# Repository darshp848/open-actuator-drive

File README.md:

# Open actuator drive

KiCad designs and simulation models for a nominal 48 V brushless actuator
drive and its support electronics. See the [humanoid upper-body project
page](https://darshpatel.xyz/projects/humanoid-upper-body) for board renders,
system context, and the simulations behind the designs.

**All designs in this repository are unfinished, unvalidated research prototypes.**
No hardware validation has been performed. Routing and KiCad checks describe the
state of the design files. Fabrication, assembly, and hardware bring-up and
testing are still open.

## Boards

| Board | KiCad source and notes | Gerbers and drill | Current state |
|---|---|---|---|
| DC bus support | [180 × 45 mm board](hardware/support-board/) | [ZIP](fab/support-board/SupportBoard/SupportBoard-gerbers.zip) | Routed. No DRC findings or open connections. Three ERC library-symbol warnings. |
| Brake resistor Rev B | [190 × 38 mm strip](hardware/brake-resistor/) | [ZIP](fab/brake-resistor/BrakeResistor/BrakeResistor-gerbers.zip) | Routed. No DRC or ERC findings. Strip cooling and the thermostat interlock need testing. |
| External capacitor bank | [101.6 × 25.4 mm board](hardware/capacitor-bank/) | [ZIP](fab/capacitor-bank/CapacitorBank/CapacitorBank-gerbers.zip) | Routed. No DRC or ERC findings. Capacitor fit and electrical behavior need testing. |
| DF40 header breakout | [Bench breakout](hardware/df40-breakouts/DF40_Header_Breakout/) | [ZIP](fab/df40-breakouts/DF40_Header_Breakout/DF40_Header_Breakout-gerbers.zip) | Routed. No DRC or ERC findings. Mating orientation and fit need checking. |
| DF40 receptacle breakout | [Bench breakout](hardware/df40-breakouts/DF40_Receptacle_Breakout/) | [ZIP](fab/df40-breakouts/DF40_Receptacle_Breakout/DF40_Receptacle_Breakout-gerbers.zip) | Routed. No DRC or ERC findings. Mating orientation and fit need checking. |
| Common logic | [Controller stack draft](hardware/wip/logic-board/) | | Partially routed, 177 unconnected items. |
| P96 power (GIM8115-36 / GIM8108-36) | [Controller stack draft](hardware/wip/power-p96/) | | Partially routed, 212 unconnected items and one silkscreen DRC finding. |
| WGG power (WGG8108-8) | [Controller stack draft](hardware/wip/power-wgg/) | | Partially routed, 258 unconnected items. |

Open each project's `.kicad_pro` in KiCad 10. The five routed boards also have
schematic PDFs, BOMs and position files. See [fabrication files](fab/) for
export settings and the scope of the checks. See the [DF40 breakout
notes](hardware/df40-breakouts/) for the pin map and bench setup.

## Earlier controllers

The [controller archive](hardware/archive/) includes the single-board X1
draft, the P57 and Unitree IM6014 design status, and a pinned link to the
separate MD80-compatible controller.

## Work still open

- Finish routing the common logic, P96 and WGG boards. Close remaining ERC and
  DRC findings, confirm motor and stack fit, and test the firmware and
  controller interfaces.
- Review the routed boards with the fabricator, check the stackup and part
  footprints, and build and inspect first articles. Check the DF40 pin mapping
  against the connector mating view and verify fit and continuity.
- Bench-test the power input and precharge, overcurrent and voltage protection,
  bus ripple and discharge, the regen chopper and the brake thermostat. Measure
  thermal behavior at the intended voltage, current, duty cycle and airflow.
  The simulations and calculations do not establish safe operating limits.
- Test the assembled drive with the intended motors and loads. Correlate the
  electrical, mechanical and thermal models with measured data.

## Simulations

| Model | What it covers |
|---|---|
| [OpenArm Simulink](simulation/openarm-simulink/) | One-arm dynamics and averaged electrical model. MATLAB R2026a with Simulink, Simscape and Robotics System Toolbox. |
| [OpenArm MuJoCo](simulation/openarm-mujoco/) | Numerical baseline with pinned upstream OpenArm assets. |
| [Virtual actuator](simulation/virtual-actuator/) | Synthetic two-joint arm and actuator plant for control experiments. |

## Licence

| Files | Licence |
|---|---|
| Original hardware sources, footprints, 3D bodies and fabrication outputs | [CERN-OHL-S-2.0](LICENSE-HARDWARE) |
| Original Python and MATLAB code and simulation models | [Apache-2.0](LICENSE-APACHE) |
| Original documentation and images | [CC BY 4.0](LICENSE-DOCS) |

The mjbots-derived controller boards and the upstream simulation assets have
their own terms. See [third-party notices](NOTICE.md).

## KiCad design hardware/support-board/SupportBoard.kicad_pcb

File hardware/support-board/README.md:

# DC bus support board

One board per arm. It handles input hot-swap and precharge, bulk capacitance,
two power/CAN chain ports, housekeeping power, the brake chopper and controlled
discharge. The [brake resistor strip](../brake-resistor/) connects to J4 for
BUS+ and BRK_SW and to J6 for the thermostat.

- [KiCad project](SupportBoard.kicad_pro) and [parts list](bom.csv)
- [Schematic PDF](../../fab/support-board/SupportBoard/SupportBoard-schematic.pdf)
- [Front and back copper review PDF](SupportBoard-layout.pdf)
- [Gerber and drill ZIP](../../fab/support-board/SupportBoard/SupportBoard-gerbers.zip)

The 180 × 45 mm, two-layer board is routed, with components on both faces.
KiCad 10.0.7 reported zero DRC findings, unconnected items and schematic
mismatches. ERC reported three library-symbol mismatch warnings for D5, D6,
and JP1. Those warnings need review before release for hardware.

## Work still open

Check arm fit, underside clearance, fabricator stackup and assembly. Validate
precharge, fault interruption, operating voltage and current, shunt sharing,
temperature rise, and the discharge circuit on hardware. The 20 A continuous
and 40 A peak figures used in the arm study were provisional design inputs.

Verify the chopper with the external resistor bank, including the relationship
between the input overvoltage lockout and the chopper threshold. The current
thermostat input inhibits forced discharge. Verify a system-level means to
stop regeneration when the thermostat opens. See the [brake resistor
notes](../brake-resistor/) for the circuit limitations identified during design.

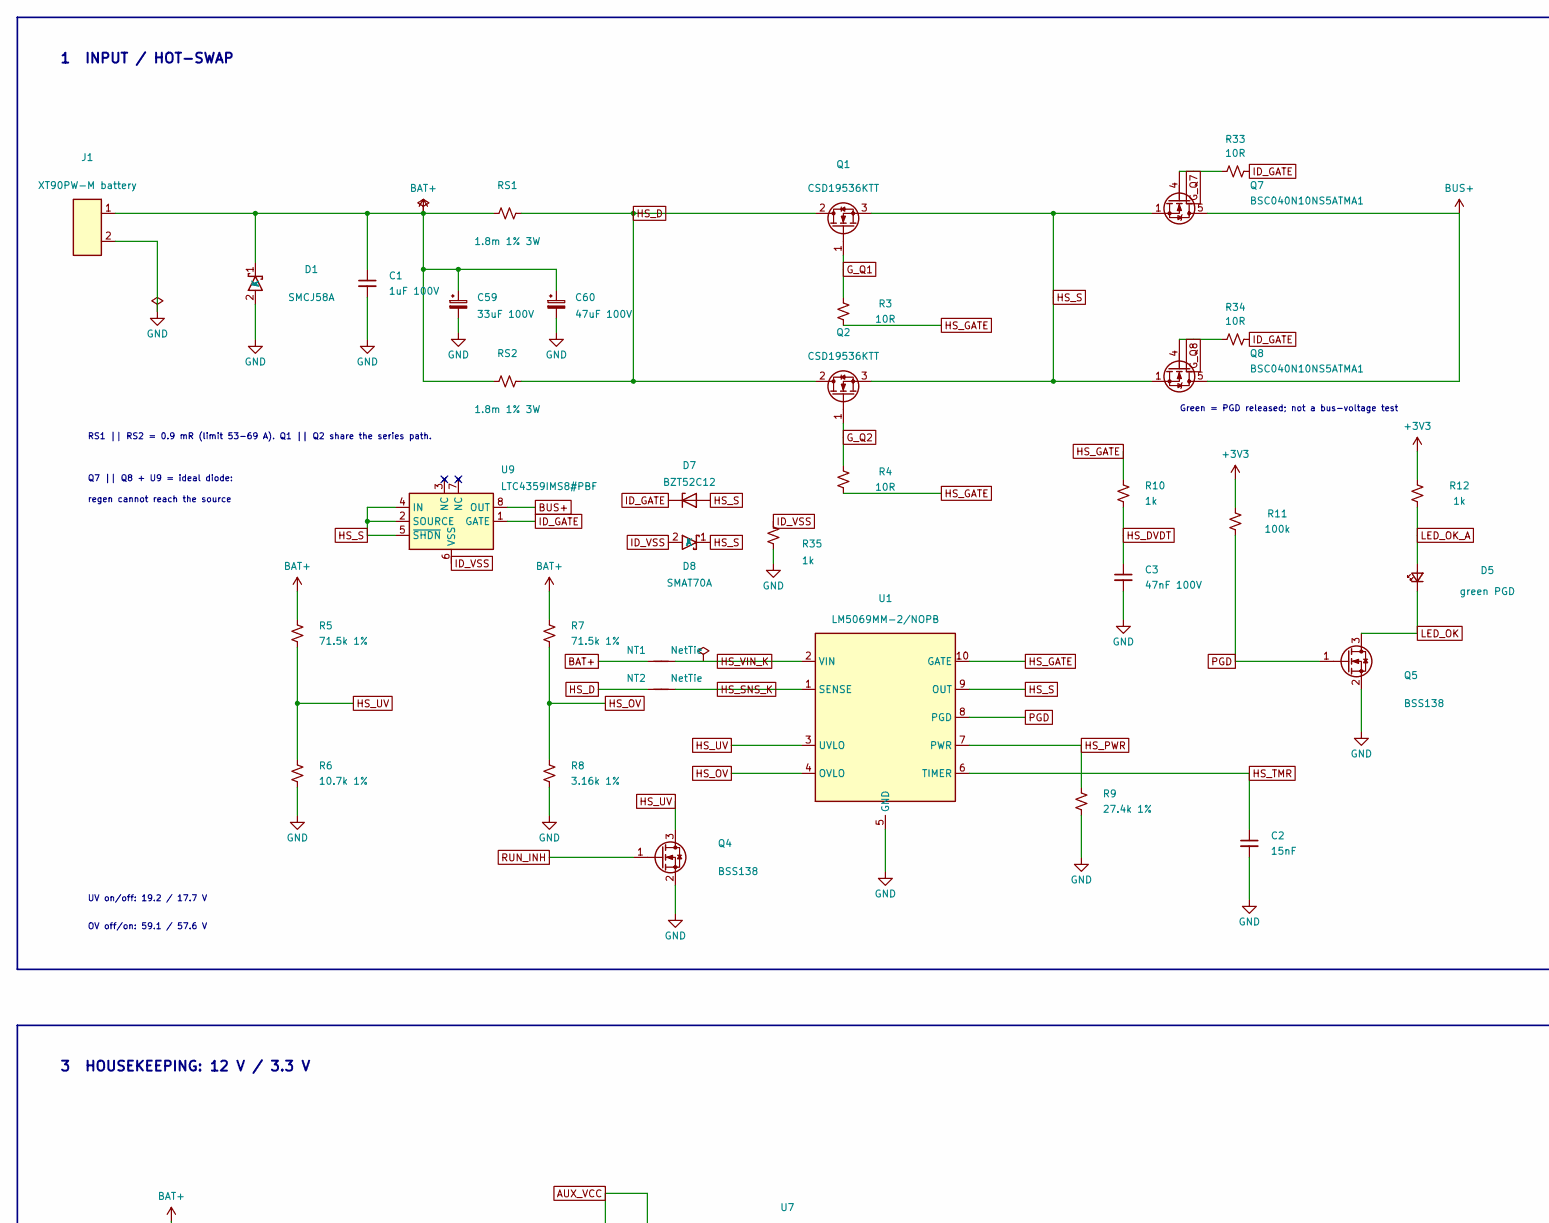
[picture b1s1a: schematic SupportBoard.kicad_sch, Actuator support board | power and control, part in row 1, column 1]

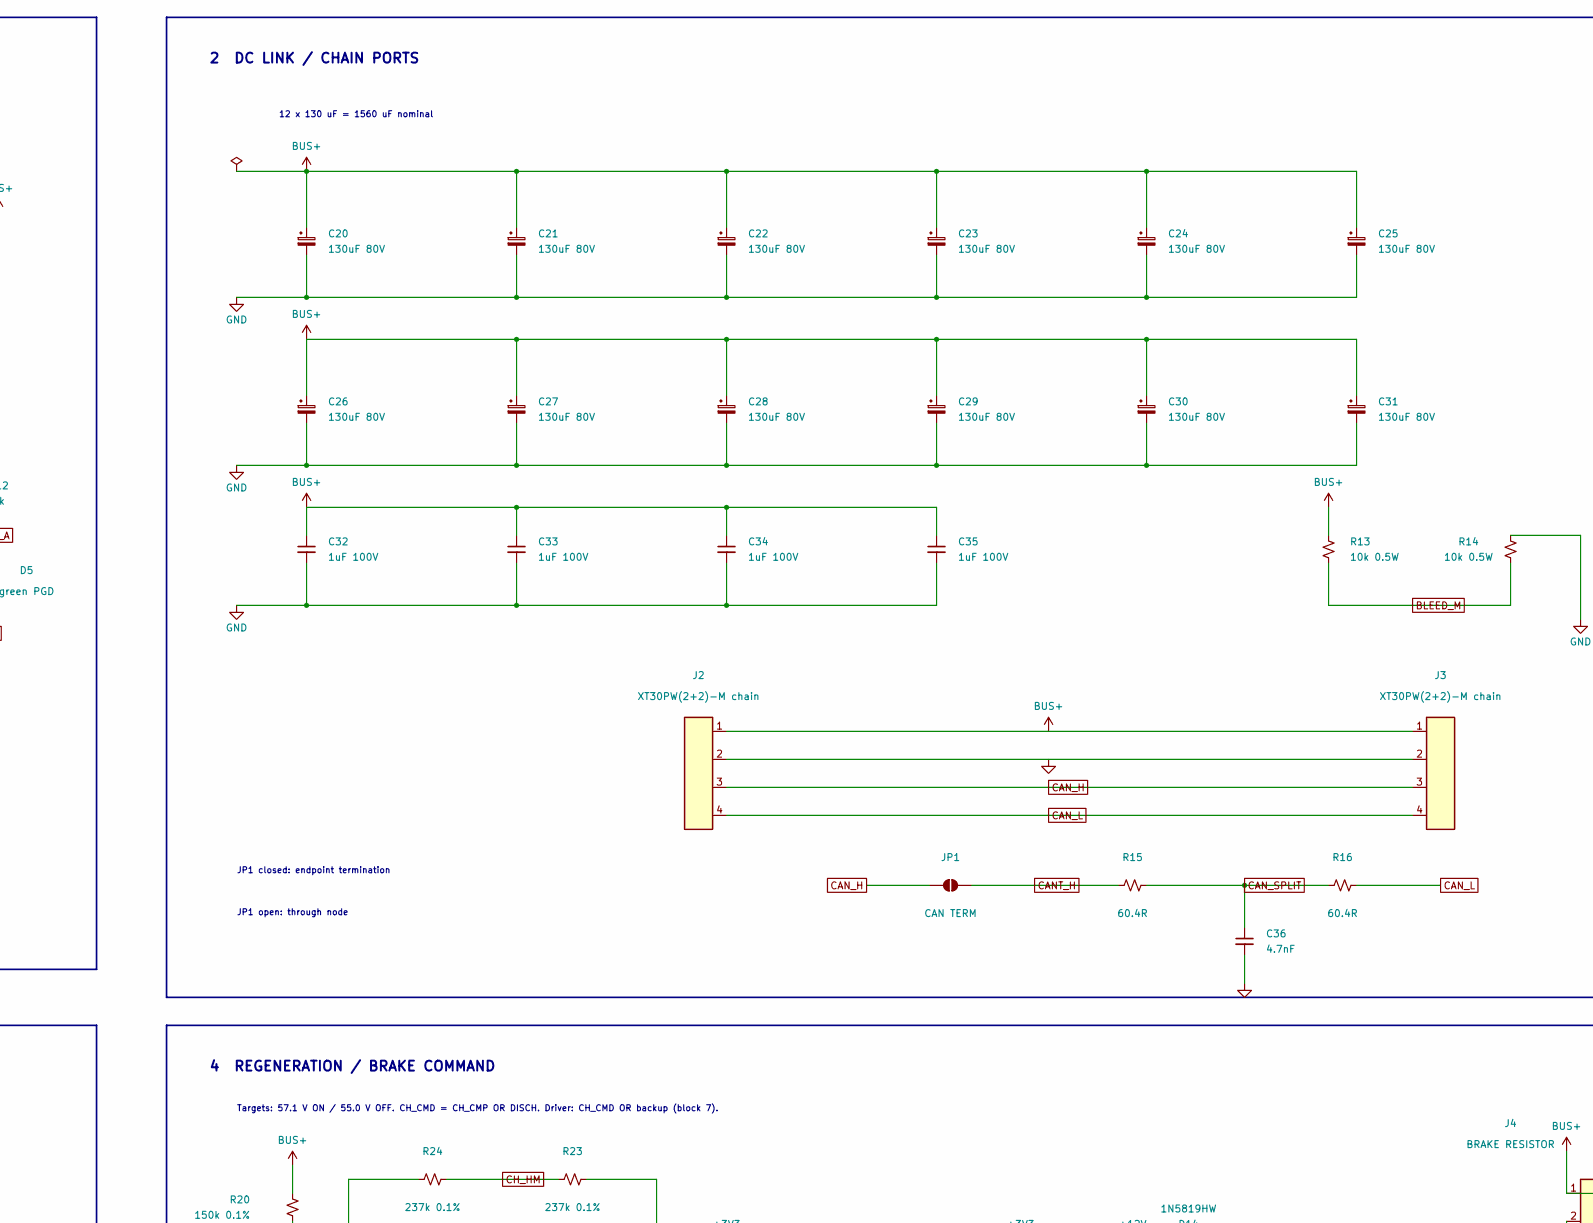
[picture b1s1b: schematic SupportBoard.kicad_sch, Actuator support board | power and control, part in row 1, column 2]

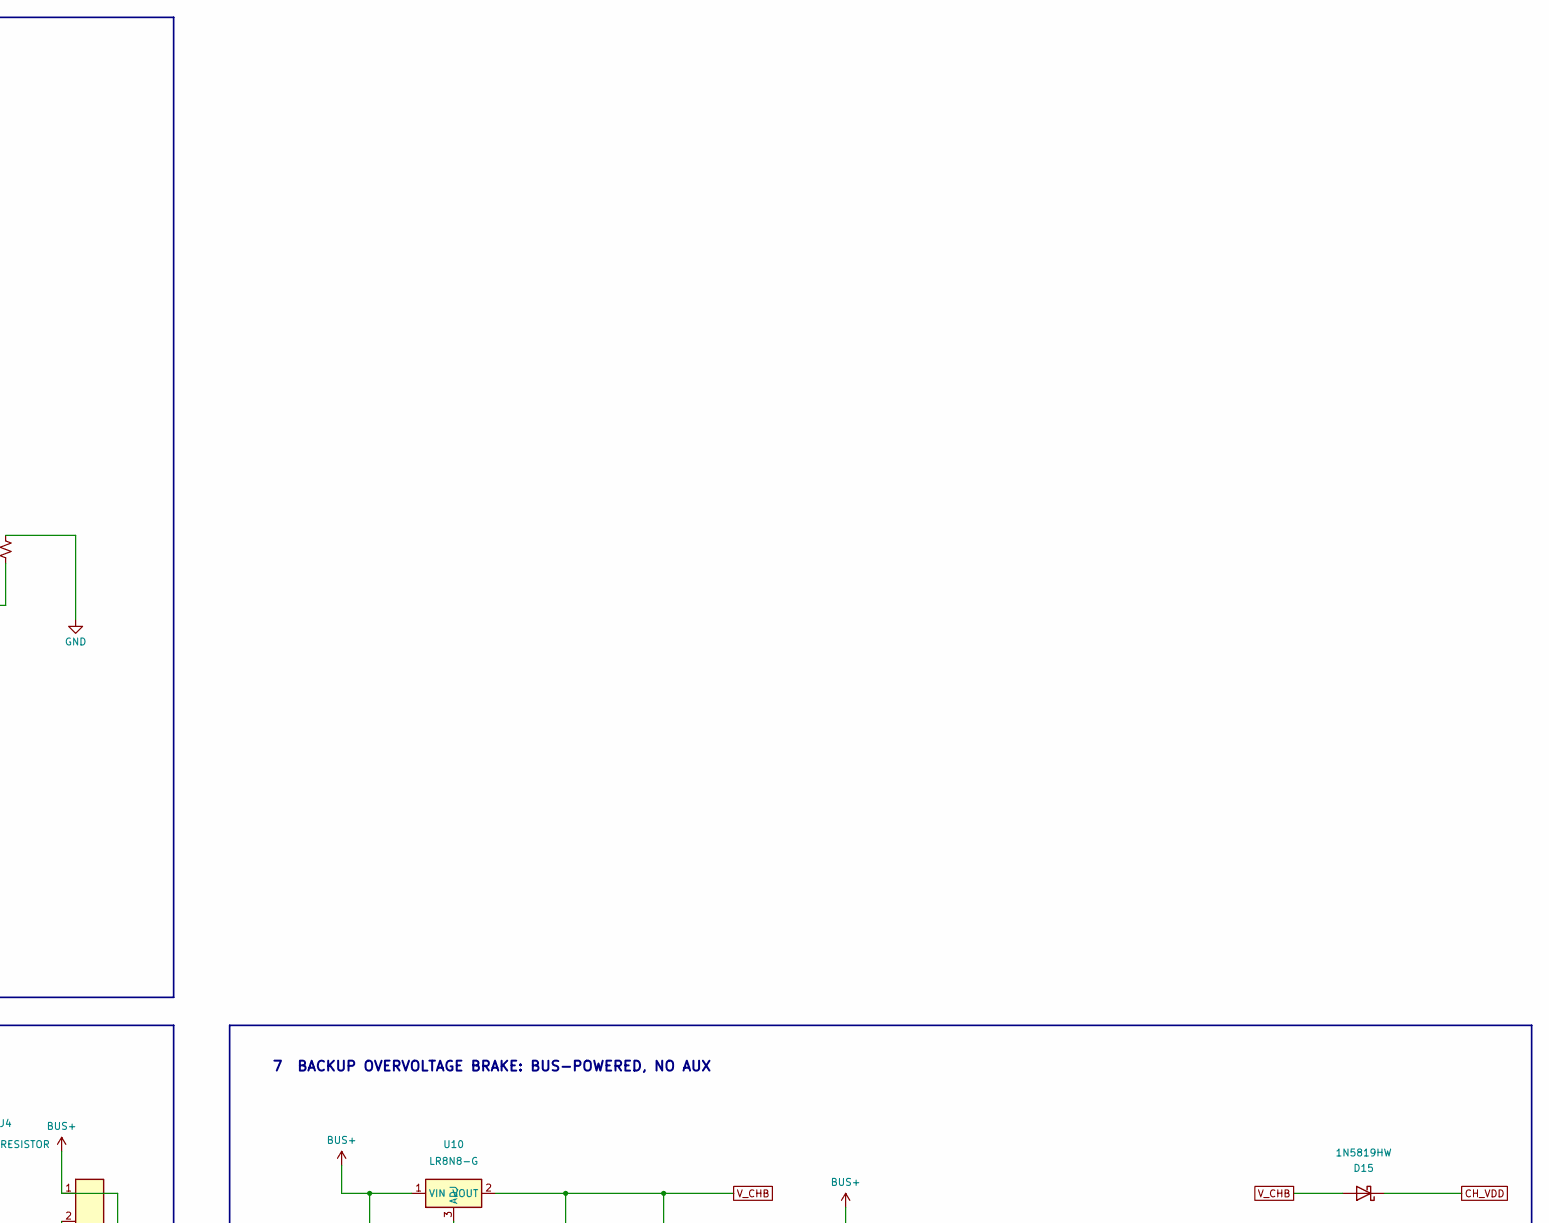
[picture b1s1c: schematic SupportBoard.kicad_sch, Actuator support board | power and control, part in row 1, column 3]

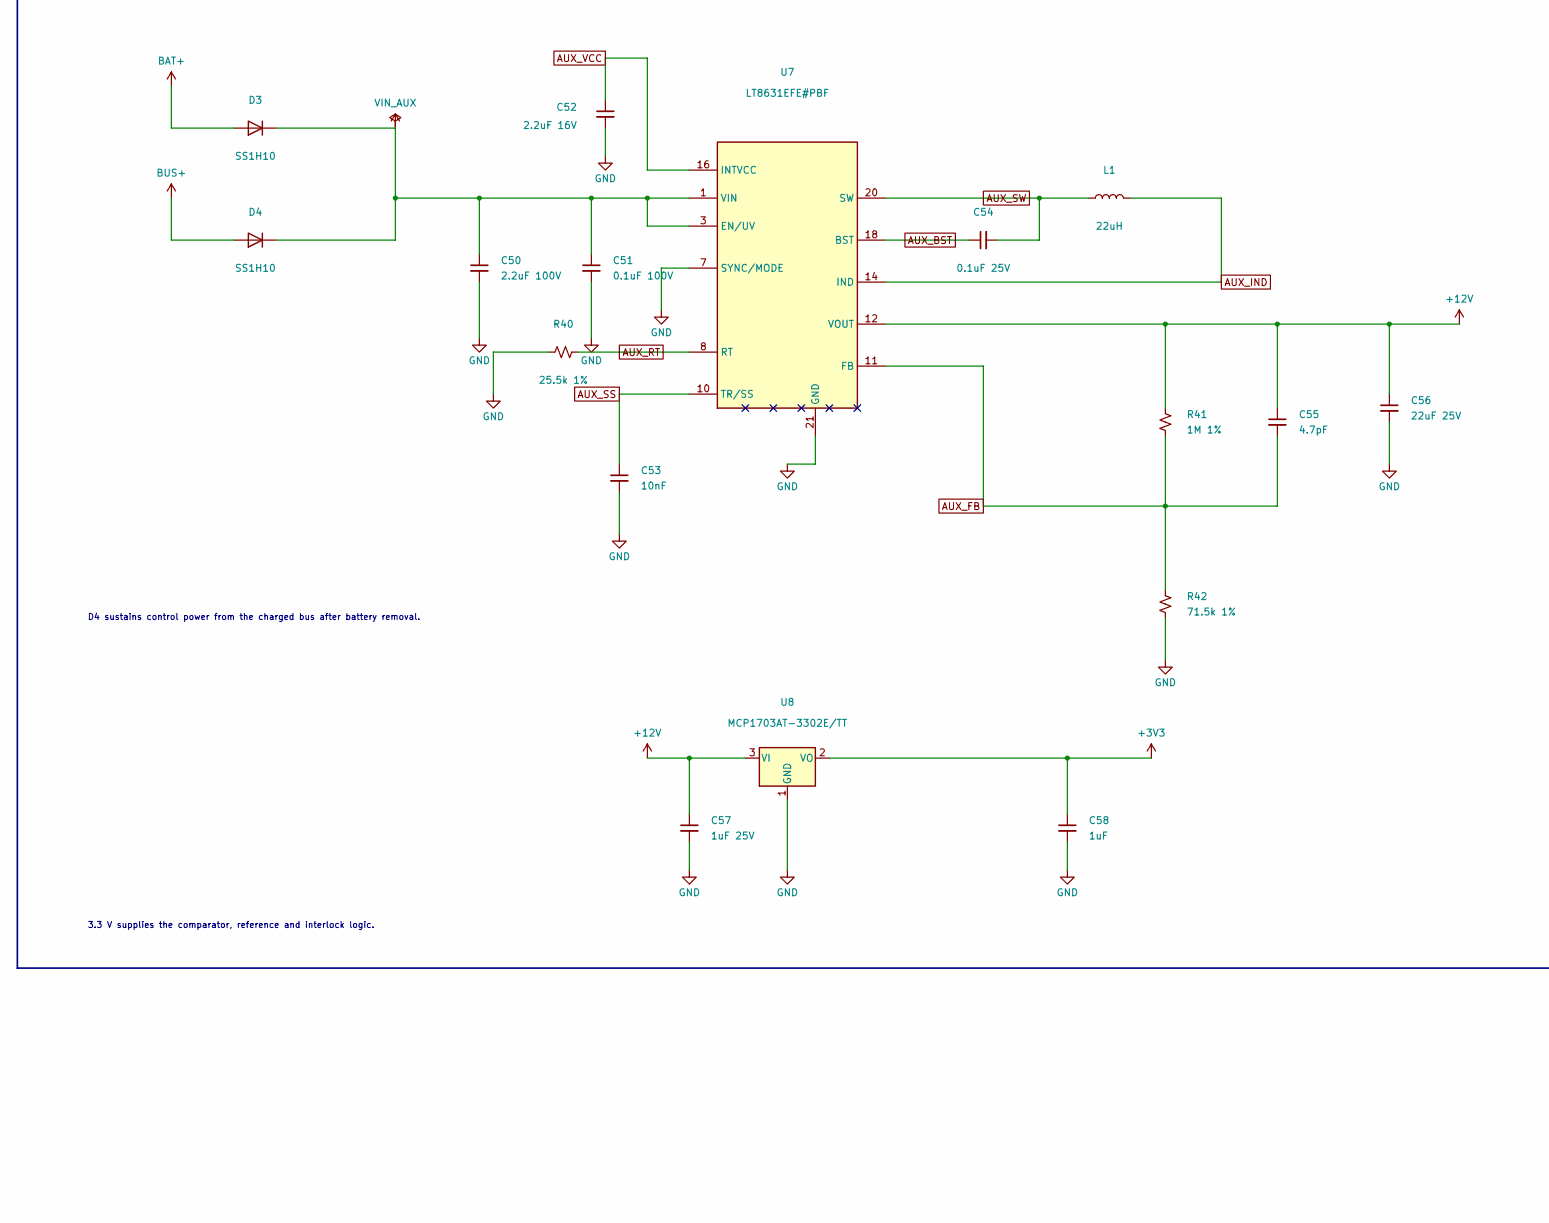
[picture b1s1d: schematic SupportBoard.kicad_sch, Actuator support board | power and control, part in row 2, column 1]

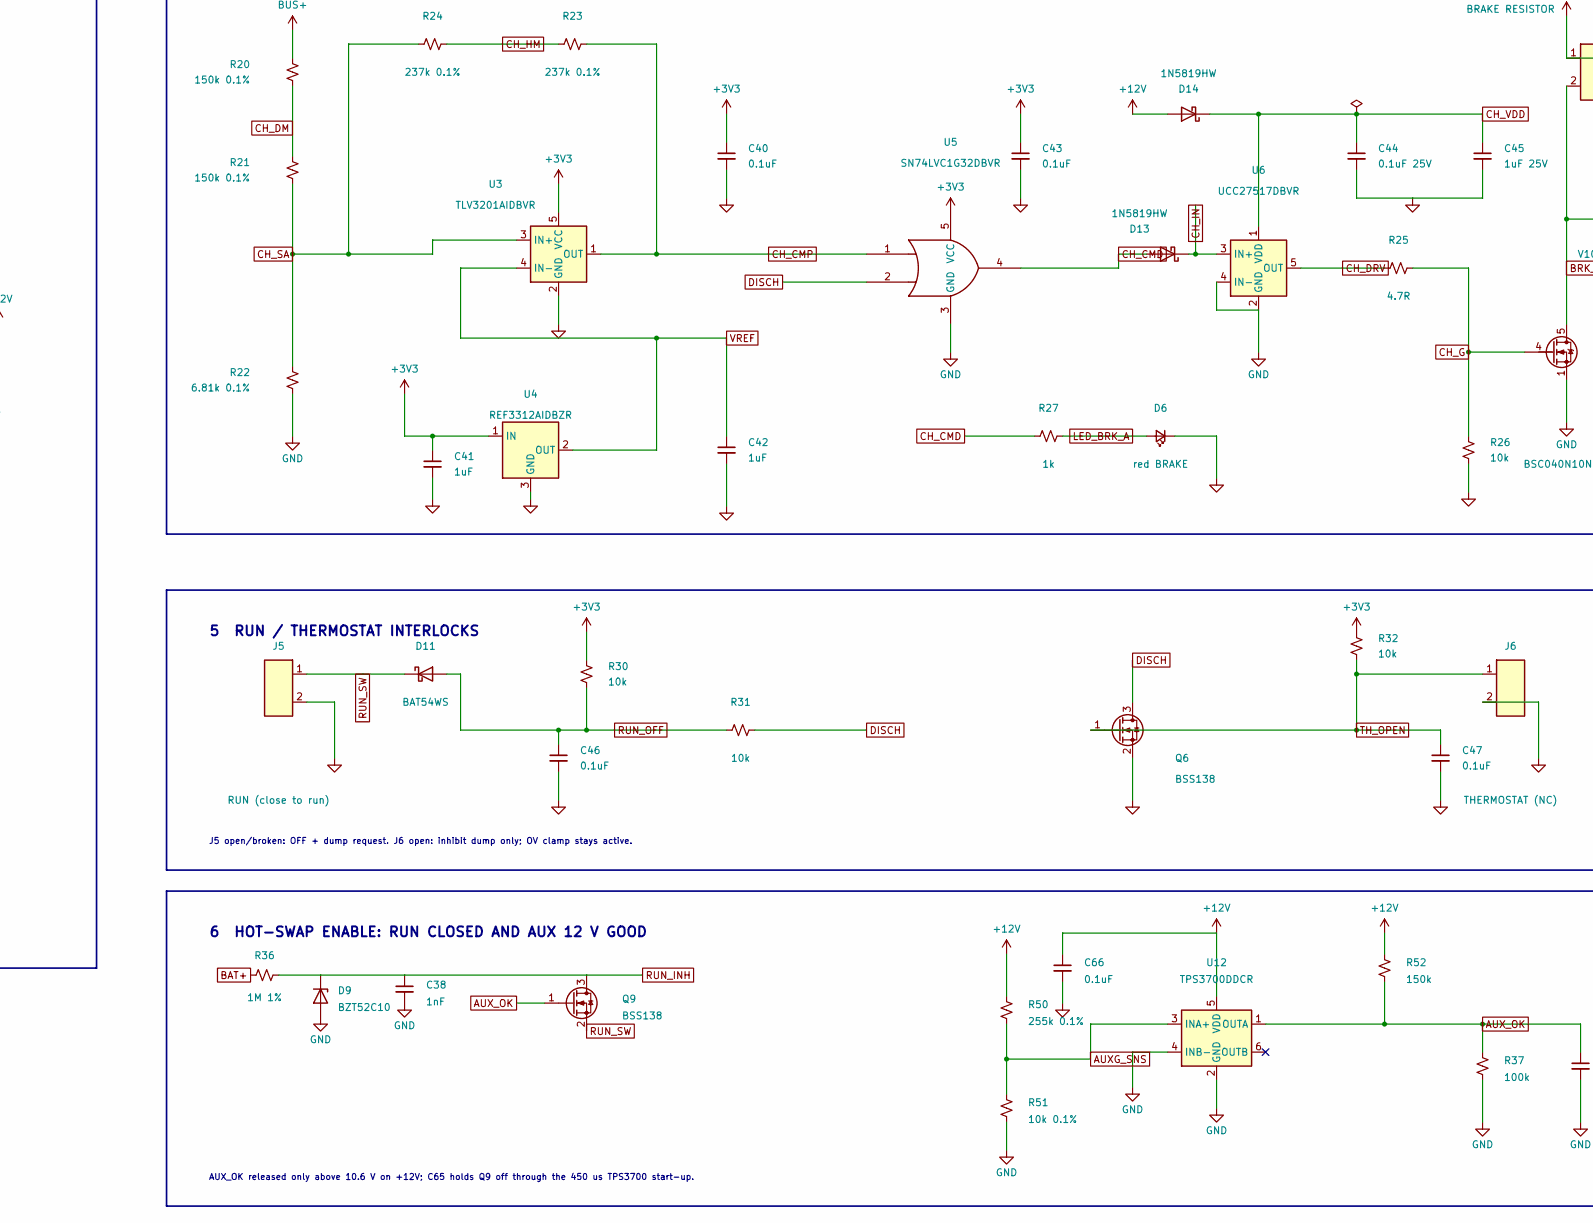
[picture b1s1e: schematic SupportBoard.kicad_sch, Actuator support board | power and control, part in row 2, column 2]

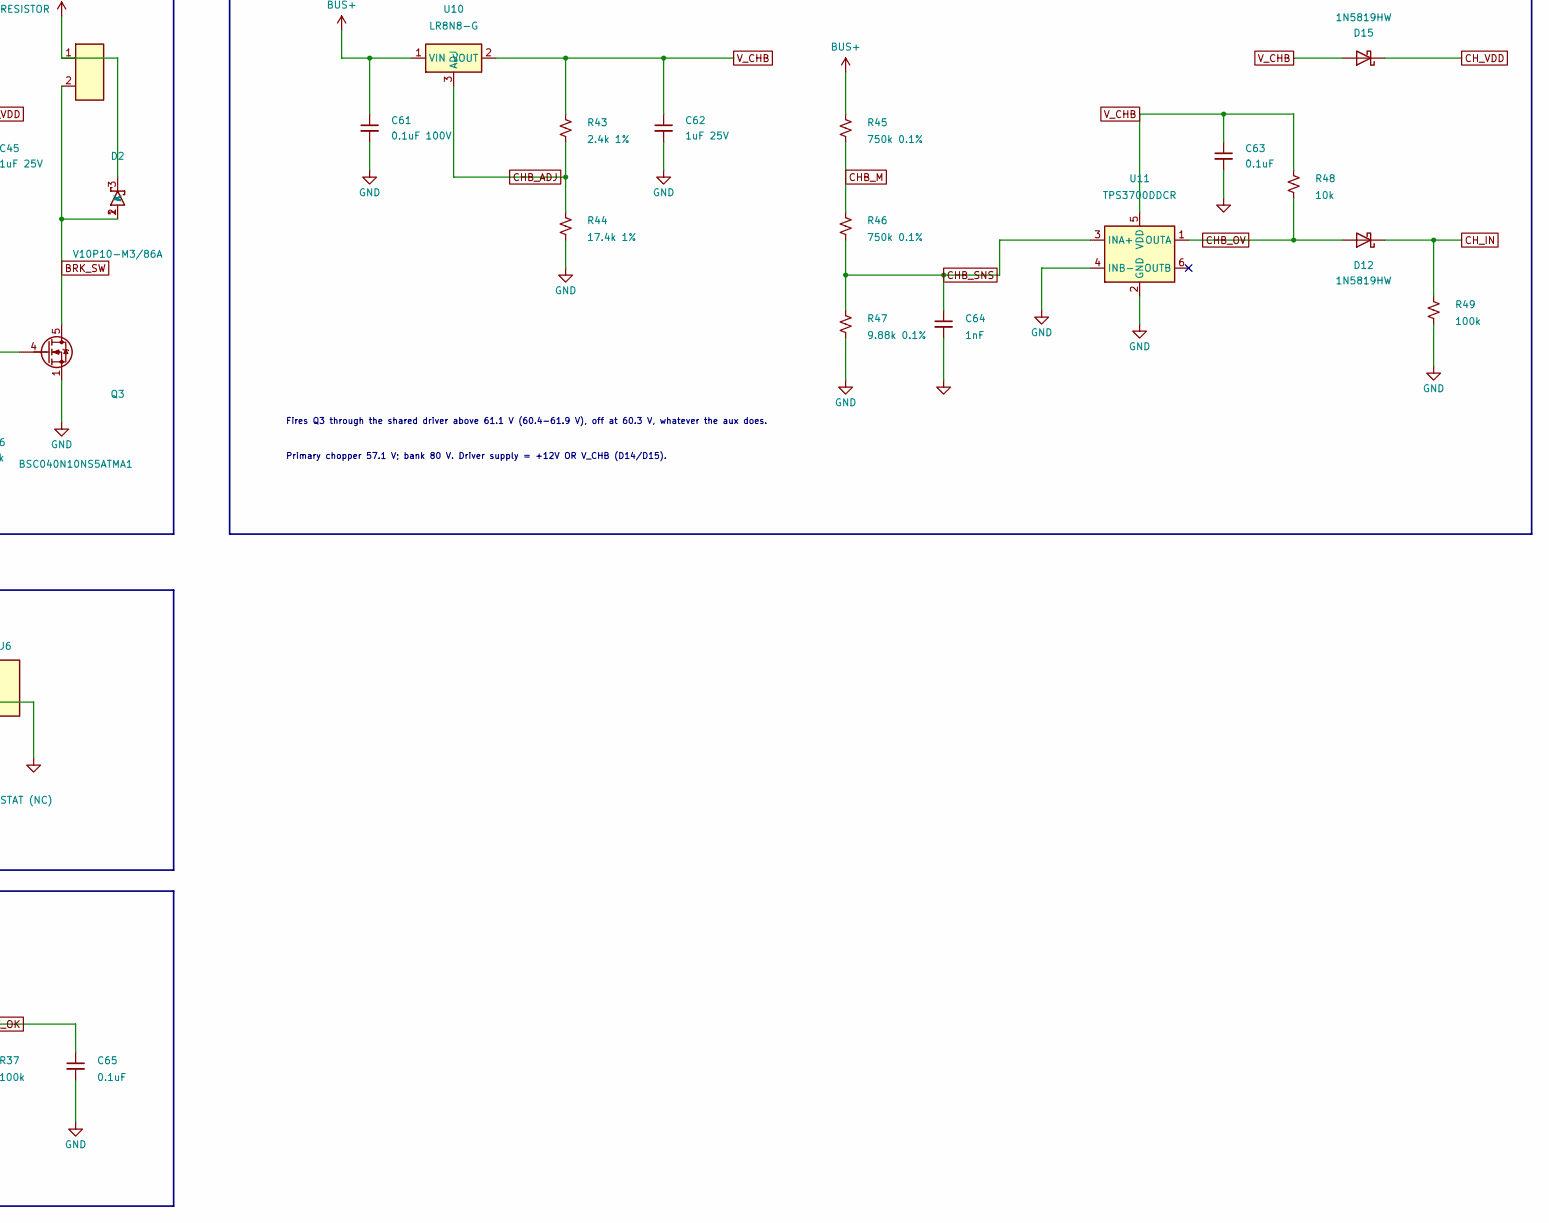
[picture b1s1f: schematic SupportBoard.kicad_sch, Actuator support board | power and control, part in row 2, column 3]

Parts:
C1, C32, C33, C34, C35: 1uF 100V; C_1210_3225Metric; MPN GRM32ER72A105KA01L
C2: 15nF; C_0603_1608Metric; MPN C0603C153K5RACTU
C3: 47nF 100V; C_0603_1608Metric; MPN C0603C473K1RACTU
C20, C21, C22, C23, C24, C25, C26, C27, C28, C29, C30, C31: 130uF 80V; TDK_B40910_10x16p5_DRAFT; MPN B40910A0137M000
C36: 4.7nF; C_0603_1608Metric; MPN GRM188R71H472KA01D
C38, C64: 1nF; C_0402_1005Metric; MPN GRM155R71H102KA01D
C40, C43, C46, C47, C63, C65, C66: 0.1uF; C_0402_1005Metric; MPN GCM155R71E104KE02D
C41, C42, C58: 1uF; C_0603_1608Metric; MPN C1608X7R1E105K080AE
C44, C54: 0.1uF 25V; C_0402_1005Metric; MPN GCM155R71E104KE02D
C45, C57, C62: 1uF 25V; C_0603_1608Metric; MPN C1608X7R1E105K080AE
C50: 2.2uF 100V; C_1210_3225Metric; MPN GRM32ER72A225KA35L
C51, C61: 0.1uF 100V; C_0603_1608Metric; MPN GCJ188R72A104KA01D
C52: 2.2uF 16V; C_0603_1608Metric; MPN C1608X7R1C225K080AC
C53: 10nF; C_0402_1005Metric; MPN GRM155R71H103KA88D
C55: 4.7pF; C_0402_1005Metric; MPN GRM1555C1H4R7CA01D
C56: 22uF 25V; C_1210_3225Metric; MPN C3225X7R1E226M250AB
C59: 33uF 100V; CP_Elec_10x12.6; MPN 875575961005
C60: 47uF 100V; CP_Elec_10x10.5; MPN EEE-FN2A470UP
D1: SMCJ58A; D_SMC; MPN SMCJ58A-M3/57T
D2: V10P10-M3/86A; TO-277A; MPN V10P10-M3/86A
D3, D4: SS1H10; D_SMA; MPN SS1H10-E3/61T
D5: green PGD; LED_0603_1608Metric; MPN 150060GS75000
D6: red BRAKE; LED_0603_1608Metric; MPN 150060RS75000
D7: BZT52C12; D_SOD-123; MPN BZT52C12-7-F
D8: SMAT70A; D_SMA; MPN SMAT70A
D9: BZT52C10; D_SOD-123; MPN BZT52C10-7-F
D11: BAT54WS; D_SOD-323; MPN BAT54WS-7-F
D12, D13, D14, D15: 1N5819HW; D_SOD-123; MPN 1N5819HW-7-F
J1: XT90PW-M battery; AMASS_XT90PW-M_1x02_P10.90mm_Horizontal; MPN XT90PW-M
J2, J3: XT30PW(2+2)-M chain; XT30PW22M; MPN XT30PW(2+2)-M.G.B
J4: BRAKE RESISTOR; PowerWire_P8
J5: RUN (close to run); JST_PH_B2B-PH-K_1x02_P2.00mm_Vertical; MPN B2B-PH-K-S
J6: THERMOSTAT (NC); JST_PH_B2B-PH-K_1x02_P2.00mm_Vertical; MPN B2B-PH-K-S
JP1: CAN TERM; SolderJumper-2_P1.3mm_Open_RoundedPad1.0x1.5mm
L1: 22uH; L_Vishay_IHLP-2525; MPN IHLP2525CZER220M8A
NT1, NT2: NetTie; NetTie-2_SMD_Pad0.5mm
Q1, Q2: CSD19536KTT; TO-263-2; MPN CSD19536KTTT
Q3, Q7, Q8: BSC040N10NS5ATMA1; TDSON-8-1; MPN BSC040N10NS5ATMA1
Q4, Q5, Q6, Q9: BSS138; SOT-23; MPN BSS138
R3, R4, R33, R34: 10R; R_0603_1608Metric; MPN RC0603FR-0710RL
R5, R7: 71.5k 1%; R_0603_1608Metric; MPN RC0603FR-0771K5L
R6: 10.7k 1%; R_0603_1608Metric; MPN RC0603FR-0710K7L
R8: 3.16k 1%; R_0603_1608Metric; MPN RC0603FR-073K16L
R9: 27.4k 1%; R_0603_1608Metric; MPN RC0603FR-0727K4L
R10, R35: 1k; R_0603_1608Metric; MPN RC0603FR-071KL
R11, R37, R49: 100k; R_0402_1005Metric; MPN RC0402FR-07100KL
R12, R27: 1k; R_0402_1005Metric; MPN RC0402FR-071KL
R13, R14: 10k 0.5W; R_2512_6332Metric; MPN RC2512FK-0710KL
R15, R16: 60.4R; R_0603_1608Metric; MPN RC0603FR-0760R4L
R20, R21: 150k 0.1%; R_0603_1608Metric; MPN TNPW0603150KBETA
R22: 6.81k 0.1%; R_0603_1608Metric; MPN TNPW06036K81BETA
R23, R24: 237k 0.1%; R_0603_1608Metric; MPN TNPW0603237KBETA
R25: 4.7R; R_0603_1608Metric; MPN RC0603FR-074R7L
R26, R30, R31, R32, R48: 10k; R_0402_1005Metric; MPN RC0402FR-0710KL
R36: 1M 1%; R_0805_2012Metric; MPN RC0805FR-071ML
R40: 25.5k 1%; R_0402_1005Metric; MPN RC0402FR-0725K5L
R41: 1M 1%; R_0402_1005Metric; MPN RC0402FR-071ML
R42: 71.5k 1%; R_0402_1005Metric; MPN RC0402FR-0771K5L
R43: 2.4k 1%; R_0603_1608Metric; MPN RC0603FR-072K4L
R44: 17.4k 1%; R_0603_1608Metric; MPN RC0603FR-0717K4L
R45, R46: 750k 0.1%; R_0805_2012Metric; MPN TNPW0805750KBEEA
R47: 9.88k 0.1%; R_0603_1608Metric; MPN TNPW06039K88BEEA
R50: 255k 0.1%; R_0603_1608Metric; MPN TNPW0603255KBEEA
R51: 10k 0.1%; R_0603_1608Metric; MPN TNPW060310K0BEEA
R52: 150k; R_0402_1005Metric; MPN RC0402FR-07150KL
RS1, RS2: 1.8m 1% 3W; R_2512_6332Metric; MPN CSS2H-2512K-1L80FE
U1: LM5069MM-2/NOPB; VSSOP-10_3x3mm_P0.5mm; MPN LM5069MM-2/NOPB
U3: TLV3201AIDBVR; SOT-23-5; MPN TLV3201AIDBVR
U4: REF3312AIDBZR; SOT-23; MPN REF3312AIDBZR
U5: SN74LVC1G32DBVR; SOT-23-5; MPN SN74LVC1G32DBVR
U6: UCC27517DBVR; SOT-23-5; MPN UCC27517DBVT
U7: LT8631EFE#PBF; Analog_FE20-16_TSSOP-20-1EP_4.4x6.5mm_P0.65mm_EP2.74x3.86mm; MPN LT8631EFE#PBF
U8: MCP1703AT-3302E/TT; SOT-23; MPN MCP1703AT-3302E/TT
U9: LTC4359IMS8#PBF; MSOP-8_3x3mm_P0.65mm; MPN LTC4359IMS8#PBF
U10: LR8N8-G; SOT-89-3; MPN LR8N8-G
U11, U12: TPS3700DDCR; TSOT-23-6; MPN TPS3700DDCR

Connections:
+3V3: C40.1, C41.1, C43.1, C58.1, R11.2, R12.2, R30.1, R32.1, U3.5 (VCC), U4.1 (IN), U5.5 (VCC), U8.2 (VO)
+12V: C55.1, C56.1, C57.1, C66.1, D14.2 (A), R41.1, R50.1, R52.1, U7.12 (VOUT), U8.3 (VI), U12.5 (VDD)
AUXG_SNS: R50.2, R51.1, U12.3 (INA+)
AUX_BST: C54.1, U7.18 (BST)
AUX_FB: C55.2, R41.2, R42.1, U7.11 (FB)
AUX_IND: L1.2, U7.14 (IND)
AUX_OK: C65.1, Q9.1 (G), R37.1, R52.2, U12.1 (OUTA)
AUX_RT: R40.1, U7.8 (RT)
AUX_SS: C53.1, U7.10 (TR/SS)
AUX_SW: C54.2, L1.1, U7.20 (SW)
AUX_VCC: C52.1, U7.16 (INTVCC)
BAT+: C1.1, C59.1, C60.1, D1.1 (K), D3.2 (A), J1.1, NT1.1, R5.1, R7.1, R36.1, RS1.1, RS2.1
BLEED_M: R13.2, R14.1
BRK_SW: D2.1 (A), D2.2 (A), J4.2, Q3.5 (D)
BUS+: C20.1, C21.1, C22.1, C23.1, C24.1, C25.1, C26.1, C27.1, C28.1, C29.1, C30.1, C31.1, C32.1, C33.1, C34.1, C35.1, C61.1, D2.3 (K), D4.2 (A), J2.1, J3.1, J4.1, Q7.5 (D), Q8.5 (D), R13.1, R20.1, R45.1, U9.8 (OUT), U10.1 (VIN)
CANT_H: JP1.2 (B), R15.1
CAN_H: J2.3, J3.3, JP1.1 (A)
CAN_L: J2.4, J3.4, R16.2
CAN_SPLIT: C36.1, R15.2, R16.1
CHB_ADJ: R43.2, R44.1, U10.3 (ADJ)
CHB_M: R45.2, R46.1
CHB_OV: D12.2 (A), R48.2, U11.1 (OUTA)
CHB_SNS: C64.1, R46.2, R47.1, U11.3 (INA+)
CH_CMD: D13.2 (A), R27.1, U5.4
CH_CMP: R23.1, U3.1 (OUT), U5.1
CH_DM: R20.2, R21.1
CH_DRV: R25.1, U6.5 (OUT)
CH_G: Q3.4 (G), R25.2, R26.1
CH_HM: R23.2, R24.1
CH_IN: D12.1 (K), D13.1 (K), R49.1, U6.3 (IN+)
CH_SA: R21.2, R22.1, R24.2, U3.3 (IN+)
CH_VDD: C44.1, C45.1, D14.1 (K), D15.1 (K), U6.1 (VDD)
DISCH: Q6.3 (D), R31.2, U5.2
GND: C1.2, C2.2, C3.2, C20.2, C21.2, C22.2, C23.2, C24.2, C25.2, C26.2, C27.2, C28.2, C29.2, C30.2, C31.2, C32.2, C33.2, C34.2, C35.2, C36.2, C38.2, C40.2, C41.2, C42.2, C43.2, C44.2, C45.2, C46.2, C47.2, C50.2, C51.2, C52.2, C53.2, C56.2, C57.2, C58.2, C59.2, C60.2, C61.2, C62.2, C63.2, C64.2, C65.2, C66.2, D1.2 (A), D6.1 (K), D9.2 (A), J1.2, J2.2, J3.2, J5.2, J6.2, Q3.1 (S), Q3.2 (S), Q3.3 (S), Q4.2 (S), Q5.2 (S), Q6.2 (S), R6.2, R8.2, R9.2, R14.2, R22.2, R26.2, R35.2, R37.2, R40.2, R42.2, R44.2, R47.2, R49.2, R51.2, U1.5 (GND), U3.2 (GND), U4.3 (GND), U5.3 (GND), U6.2 (GND), U6.4 (IN-), U7.7 (SYNC/MODE), U7.21 (GND), U8.1 (GND), U11.2 (GND), U11.4 (INB-), U12.2 (GND), U12.4 (INB-)
G_Q1: Q1.1 (G), R3.2
G_Q2: Q2.1 (G), R4.2
G_Q7: Q7.4 (G), R33.2
G_Q8: Q8.4 (G), R34.2
HS_D: NT2.1, Q1.2 (D), Q2.2 (D), RS1.2, RS2.2
HS_DVDT: C3.1, R10.2
HS_GATE: R3.1, R4.1, R10.1, U1.10 (GATE)
HS_OV: R7.2, R8.1, U1.4 (OVLO)
HS_PWR: R9.1, U1.7 (PWR)
HS_S: D7.2 (A), D8.1 (K), Q1.3 (S), Q2.3 (S), Q7.1 (S), Q7.2 (S), Q7.3 (S), Q8.1 (S), Q8.2 (S), Q8.3 (S), U1.9 (OUT), U9.2 (SOURCE), U9.4 (IN), U9.5 (~SHDN)
HS_SNS_K: NT2.2, U1.1 (SENSE)
HS_TMR: C2.1, U1.6 (TIMER)
HS_UV: Q4.3 (D), R5.2, R6.1, U1.3 (UVLO)
HS_VIN_K: NT1.2, U1.2 (VIN)
ID_GATE: D7.1 (K), R33.1, R34.1, U9.1 (GATE)
ID_VSS: D8.2 (A), R35.1, U9.6 (VSS)
LED_BRK_A: D6.2 (A), R27.2
LED_OK: D5.1 (K), Q5.3 (D)
LED_OK_A: D5.2 (A), R12.1
PGD: Q5.1 (G), R11.1, U1.8 (PGD)
RUN_INH: C38.1, D9.1 (K), Q4.1 (G), Q9.3 (D), R36.2
RUN_OFF: C46.1, D11.2 (A), R30.2, R31.1
RUN_SW: D11.1 (K), J5.1, Q9.2 (S)
TH_OPEN: C47.1, J6.1, Q6.1 (G), R32.2
VIN_AUX: C50.1, C51.1, D3.1 (K), D4.1 (K), U7.1 (VIN), U7.3 (EN/UV)
VREF: C42.1, U3.4 (IN-), U4.2 (OUT)
V_CHB: C62.1, C63.1, D15.2 (A), R43.1, R48.1, U10.2 (VOUT), U11.5 (VDD)

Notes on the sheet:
J5 open/broken: OFF + dump request. J6 open: inhibit dump only; OV clamp stays active.
5 RUN / THERMOSTAT INTERLOCKS
4 REGENERATION / BRAKE COMMAND
6 HOT-SWAP ENABLE: RUN CLOSED AND AUX 12 V GOOD
7 BACKUP OVERVOLTAGE BRAKE: BUS-POWERED, NO AUX
Fires Q3 through the shared driver above 61.1 V (60.4-61.9 V), off at 60.3 V, whatever the aux does.
JP1 closed: endpoint termination
D4 sustains control power from the charged bus after battery removal.
AUX_OK released only above 10.6 V on +12V; C65 holds Q9 off through the 450 us TPS3700 start-up.
Targets: 57.1 V ON / 55.0 V OFF. CH_CMD = CH_CMP OR DISCH. Driver: CH_CMD OR backup (block 7).
UV on/off: 19.2 / 17.7 V
RS1 || RS2 = 0.9 mR (limit 53-69 A). Q1 || Q2 share the series path.
3 HOUSEKEEPING: 12 V / 3.3 V
Primary chopper 57.1 V; bank 80 V. Driver supply = +12V OR V_CHB (D14/D15).
Q7 || Q8 + U9 = ideal diode:
regen cannot reach the source
2 DC LINK / CHAIN PORTS
1 INPUT / HOT-SWAP
JP1 open: through node
3.3 V supplies the comparator, reference and interlock logic.
OV off/on: 59.1 / 57.6 V
12 x 130 uF = 1560 uF nominal
Green = PGD released; not a bus-voltage test
